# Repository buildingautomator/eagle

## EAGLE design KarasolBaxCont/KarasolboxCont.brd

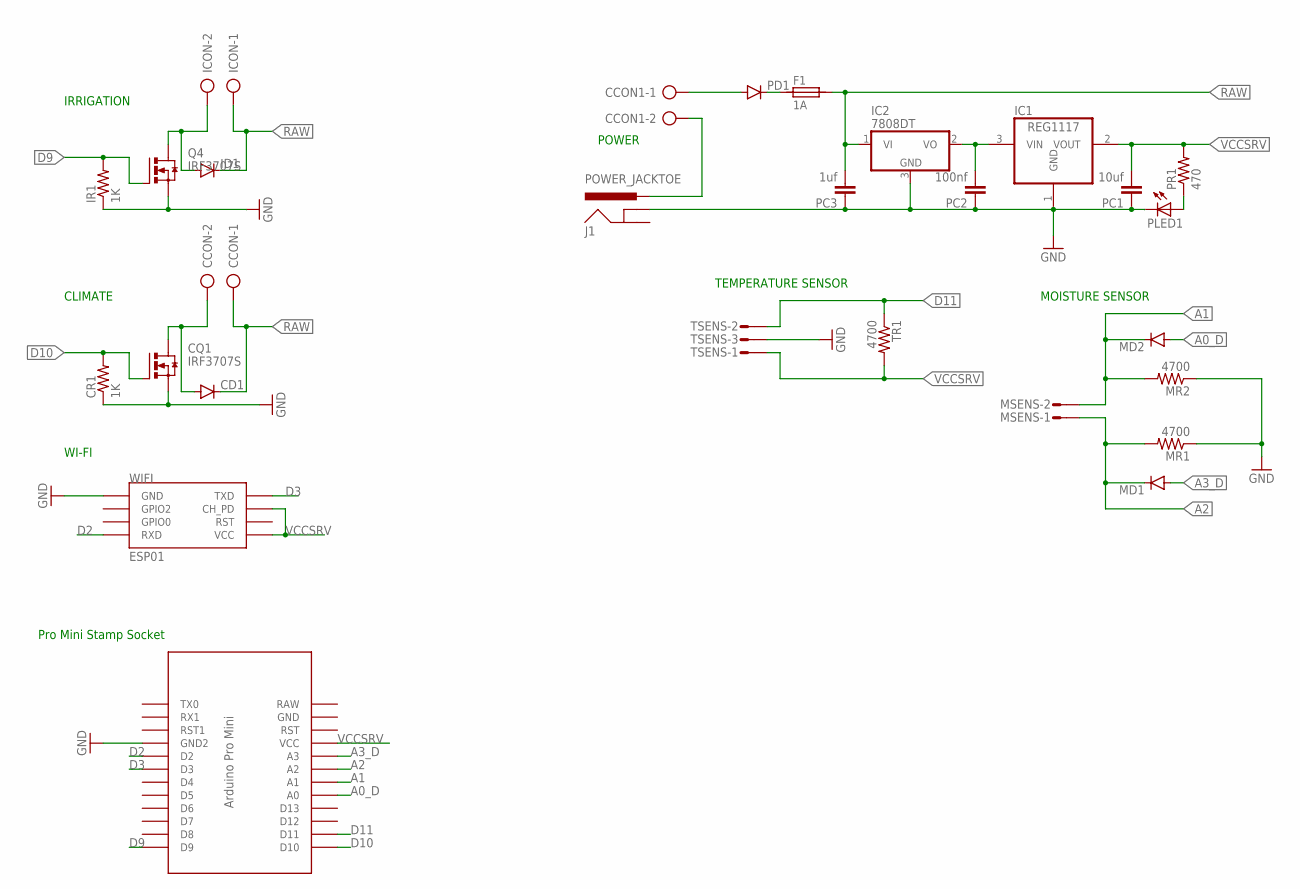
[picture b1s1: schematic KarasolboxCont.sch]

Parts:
CCON, CCON1: AK300/2
CD1: DIODESMA; SMA-DIODE
CQ1: IRF3707S; D2PACK
CR1: 1K; 0805
F1: 1A; 1820
IC1: REG1117; SOT223
IC2: 7808DT; TO252
ICON: AK300/2
ID1: DIODESMA; SMA-DIODE
IR1: 1K; 0805
J1: POWER_JACKTOE; POWER_JACK_SMD_OVERPASTE_TOE
MD1, MD2: DIODESMA; SMA-DIODE
MR1, MR2: 4700; 0805
MSENS: S02P
PC1: 10uf; 0805
PC2: 100nf; 0805
PC3: 1uf; 0805
PD1: DIODESMA; SMA-DIODE
PLED1: LEDCHIP-LED0805; CHIP-LED0805
PR1: 470; 0805
Q4: IRF3707S; D2PACK
TR1: 4700; 0805
TSENS: S03P
U$1: ABK-PRO-MINI
WIFI: ESP01

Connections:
A0_D: MD2.A, U$1.A0
A1: MD2.C, MR2.2, MSENS.2, U$1.A1
A2: MD1.C, MR1.2, MSENS.1, U$1.A2
A3_D: MD1.A, U$1.A3
D2: U$1.D2, WIFI.RX (RXD)
D3: U$1.D3, WIFI.TX (TXD)
D9: IR1.2, Q4.1 (G), U$1.D9
D10: CQ1.1 (G), CR1.2, U$1.D10
D11: TR1.1, TSENS.2, U$1.D11
GND: CQ1.3 (S), CR1.1, IC1.1 (GND), IC2.3 (GND), IR1.1, J1.GND (GNDBREAK), MR1.1, MR2.1, PC1.1, PC2.1, PC3.1, PLED1.C, Q4.3 (S), TSENS.3, U$1.GND1 (GND2), WIFI.GND
unnamed: F1.1, PD1.C
unnamed: CCON.2, CD1.A, CQ1.2 (D)
unnamed: CCON1.1, PD1.A
unnamed: ICON.2, ID1.A, Q4.2 (D)
unnamed: CCON1.2, J1.VIN0 (PWR)
unnamed: PLED1.A, PR1.1
unnamed: IC1.3 (VIN), IC2.2 (VO), PC2.2
RAW: CCON.1, CD1.C, F1.2, IC2.1 (VI), ICON.1, ID1.C, PC3.2
VCCSRV: IC1.2 (VOUT), PC1.2, PR1.2, TR1.2, TSENS.1, U$1.VCC, WIFI.CH_PD, WIFI.VCC

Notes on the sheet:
IRRIGATION
Pro Mini Stamp Socket
POWER
MOISTURE SENSOR
CLIMATE
TEMPERATURE SENSOR
WI-FI

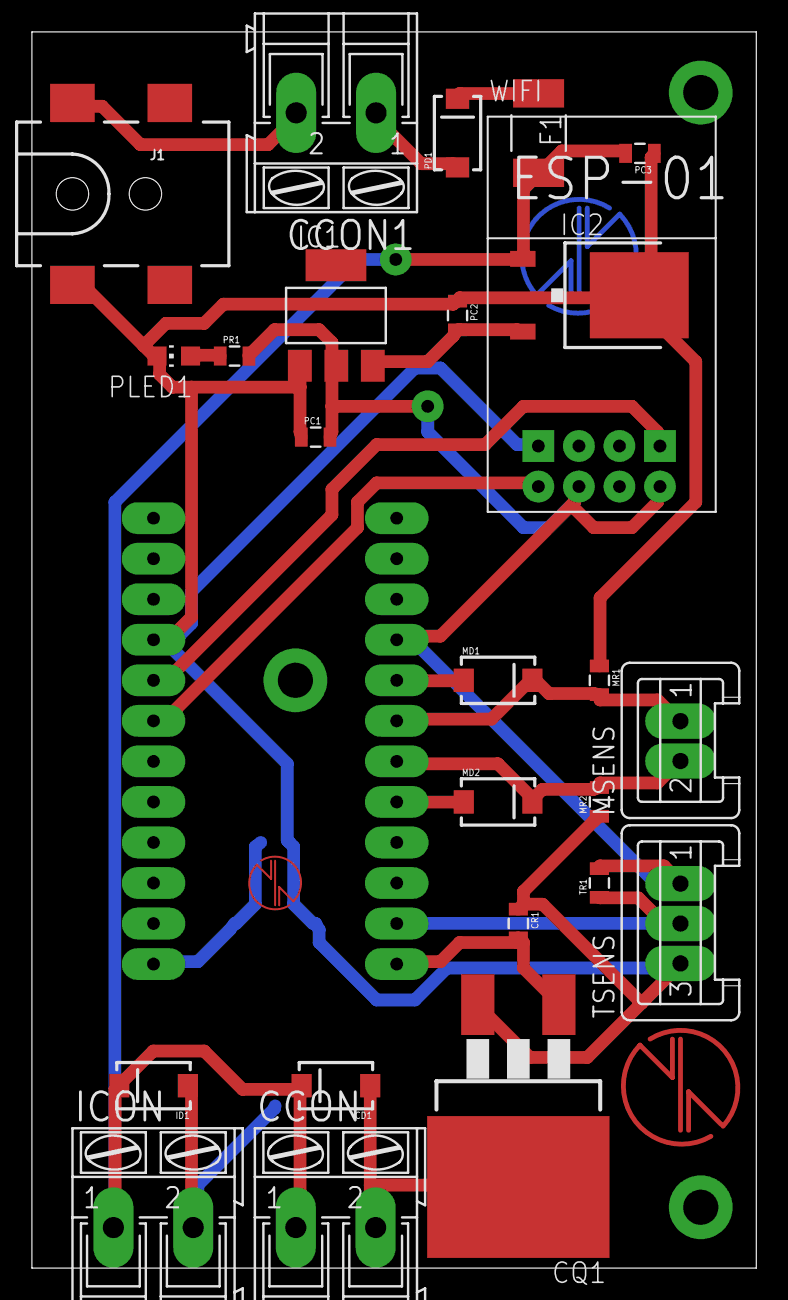
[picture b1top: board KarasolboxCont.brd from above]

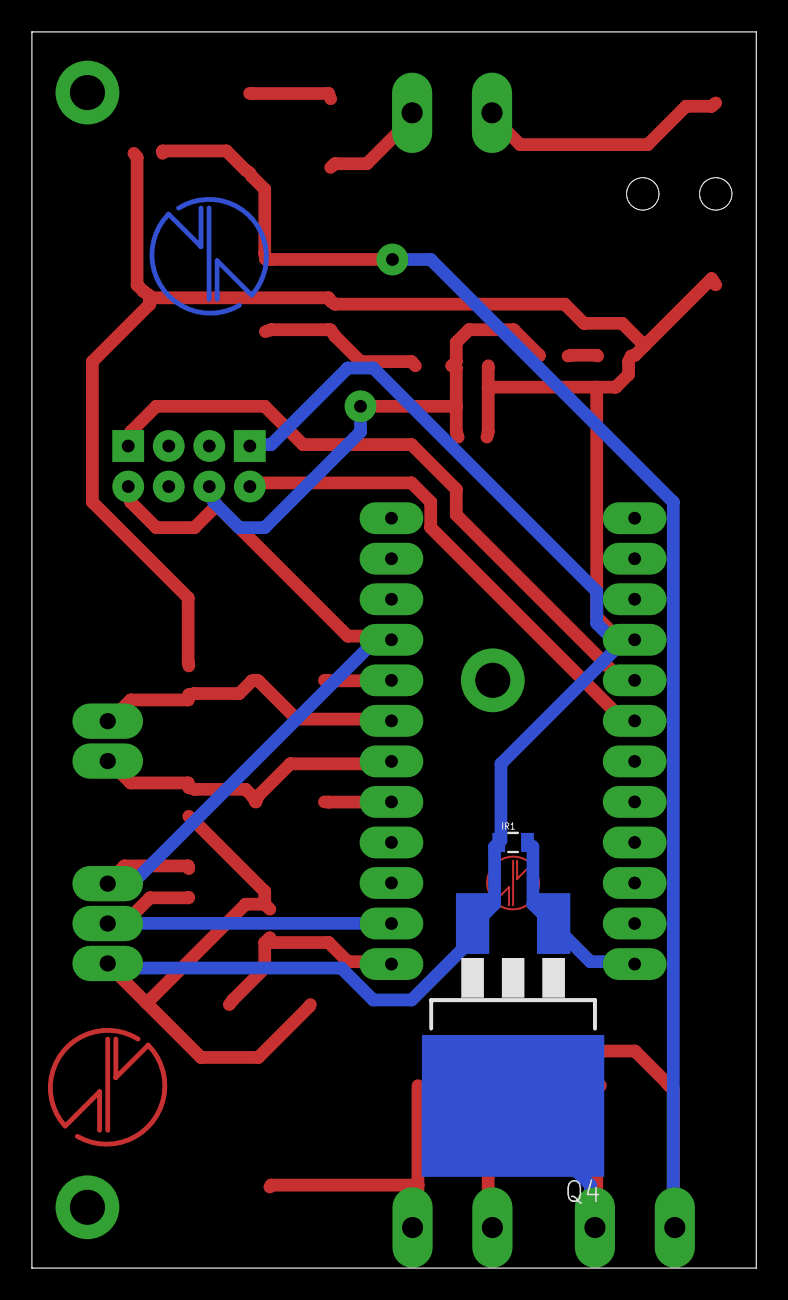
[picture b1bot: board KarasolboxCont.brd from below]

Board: 2 copper layers, 45.4 x 77.5 mm, 31 parts (3 on the bottom side), 19 nets.

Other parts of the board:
U$2: IOTECH_COPPER
U$3, U$4: IOTECH_COPPER_M

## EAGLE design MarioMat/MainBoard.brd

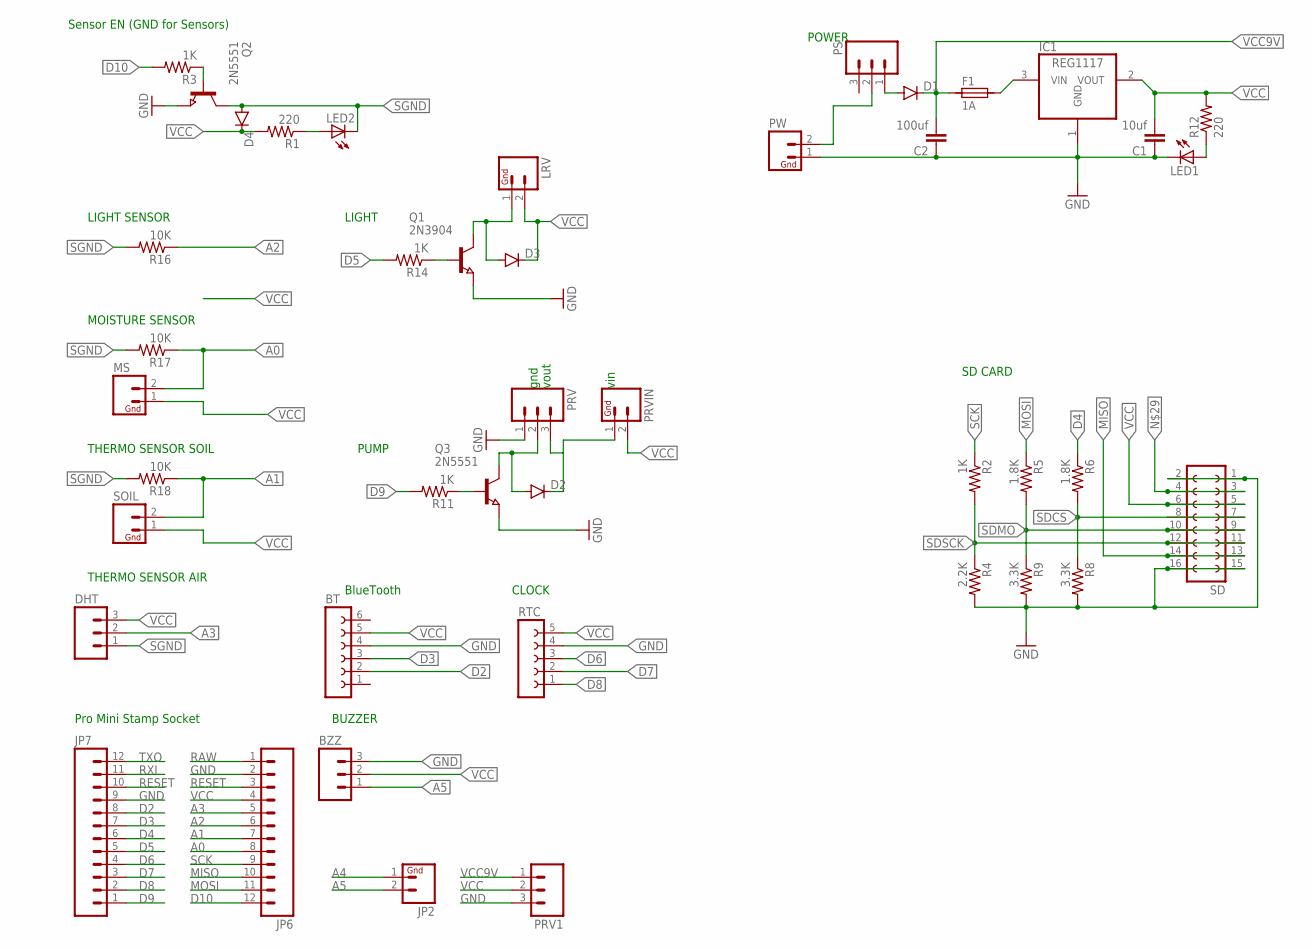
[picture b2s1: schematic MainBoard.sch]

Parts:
BT: FE06-1; FE06
BZZ: M03PTH; 1X03
C1: 10uf; 0805
C2: 100uf; 0805
D1, D2, D3, D4: DIODESMA; SMA-DIODE
DHT: M03PTH; 1X03
F1: 1A; 1820
IC1: REG1117; SOT223
JP2: M02PTH; 1X02
JP6, JP7: M12PTH; 1X12
LED1, LED2: LEDCHIP-LED0805; CHIP-LED0805
LRV: M02PTH; 1X02
MS: M02PTH; 1X02
PRV, PRV1: M03PTH; 1X03
PRVIN: M02PTH; 1X02
PS: M03PTH; 1X03
PW: M02PTH; 1X02
Q1: 2N3904; SOT23
Q2, Q3: 2N5551; SOT23
R1, R12: 220; 0805
R2, R3, R11, R14: 1K; 0805
R4: 2.2K; 0805
R5, R6: 1.8K; 0805
R8, R9: 3.3K; 0805
R16, R17, R18: 10K; 0805
RTC: FE05-1
SD: FE08-2
SOIL: M02PTH; 1X02

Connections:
A0: JP6.8, MS.2, R17.1
A1: JP6.7, R18.1, SOIL.2
A2: JP6.6, R16.1
A3: DHT.2, JP6.5
A4: JP2.1
A5: BZZ.1, JP2.2
D2: BT.2, JP7.8
D3: BT.3, JP7.7
D4: JP7.6, R6.1
D5: JP7.5, R14.2
D6: JP7.4, RTC.3
D7: JP7.3, RTC.2
D8: JP7.2, RTC.1
D9: JP7.1, R11.2
D10: JP6.12, R3.2
GND: BT.4, BZZ.3, C1.1, C2.1, IC1.1 (GND), JP6.2, JP7.9, LED1.C, PRV.1, PRV1.3, PW.1, Q1.2 (E), Q2.2 (E), Q3.2 (E), R4.2, R8.2, R9.2, RTC.4, SD.1, SD.2, SD.15, SD.16
MISO: JP6.10, SD.13, SD.14
MOSI: JP6.11, R5.1
unnamed: F1.2, IC1.3 (VIN)
unnamed: PS.2, PW.2
unnamed: D2.C, PRV.3, PRVIN.1
unnamed: D2.A, PRV.2, Q3.3 (C)
unnamed: Q3.1 (B), R11.1
unnamed: Q2.1 (B), R3.1
unnamed: LED1.A, R12.1
unnamed: D1.A, PS.1
unnamed: D3.A, LRV.1, Q1.3 (C)
unnamed: Q1.1 (B), R14.1
unnamed: LED2.A, R1.1
unnamed: SD.3, SD.4
RAW: JP6.1
RESET: JP6.3, JP7.10
RXI: JP7.11
SCK: JP6.9, R2.1
SDCS: R6.2, R8.1, SD.7, SD.8
SDMO: R5.2, R9.1, SD.9, SD.10
SDSCK: R2.2, R4.1, SD.11, SD.12
SGND: D4.A, DHT.1, LED2.C, Q2.3 (C), R16.2, R17.2, R18.2
TXO: JP7.12
VCC: BT.5, BZZ.2, C1.2, D3.C, D4.C, DHT.3, IC1.2 (VOUT), JP6.4, LRV.2, MS.1, PRV1.2, PRVIN.2, R1.2, R12.2, RTC.5, SD.5, SD.6, SOIL.1
VCC9V: C2.2, D1.C, F1.1, PRV1.1

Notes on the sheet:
PUMP
Pro Mini Stamp Socket
Sensor EN (GND for Sensors)
POWER
LIGHT
LIGHT SENSOR
MOISTURE SENSOR
THERMO SENSOR SOIL
THERMO SENSOR AIR
CLOCK
BlueTooth
SD CARD
vin
vout
gnd
BUZZER

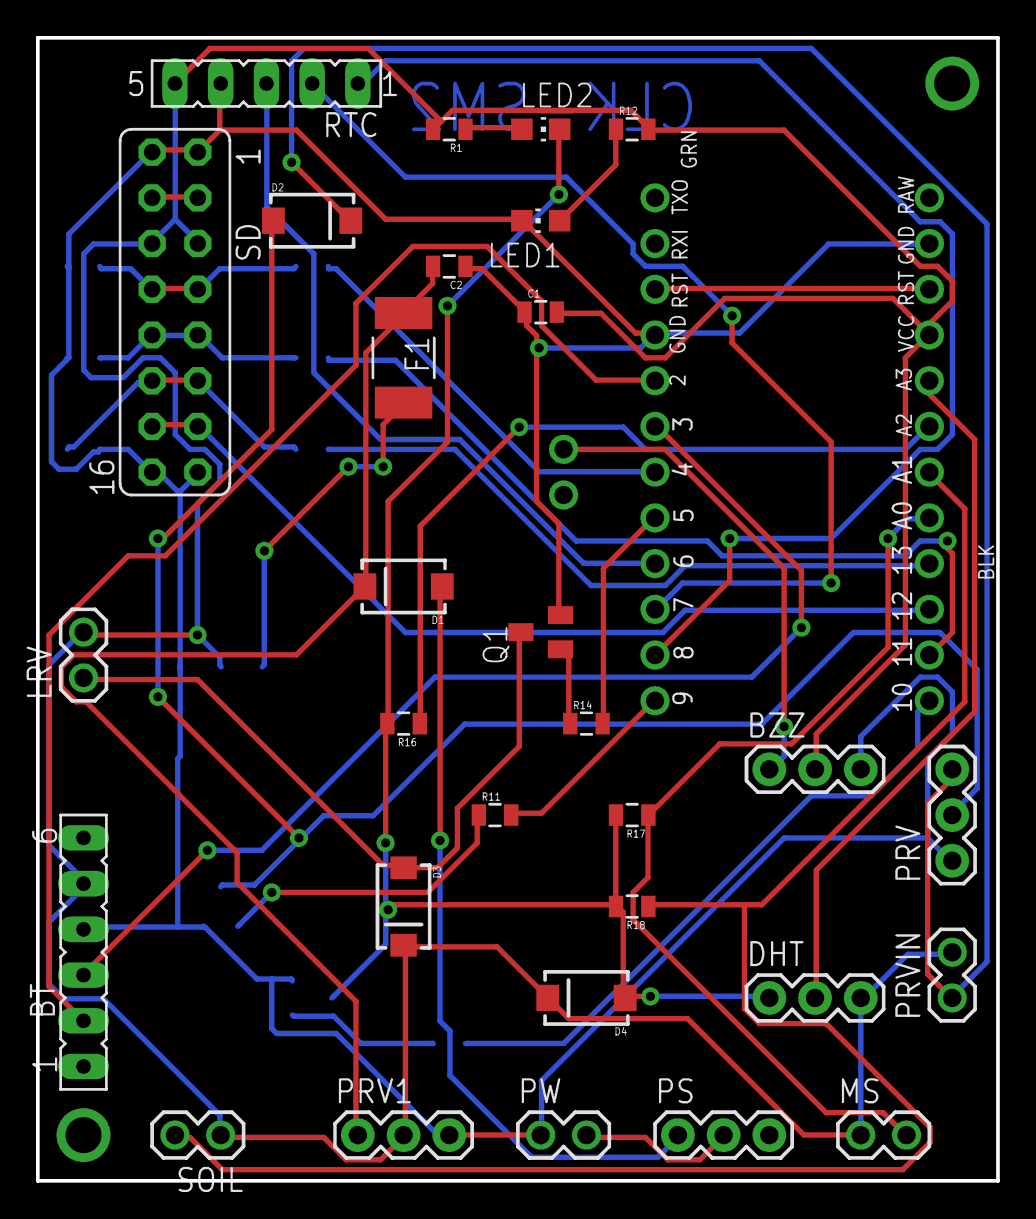
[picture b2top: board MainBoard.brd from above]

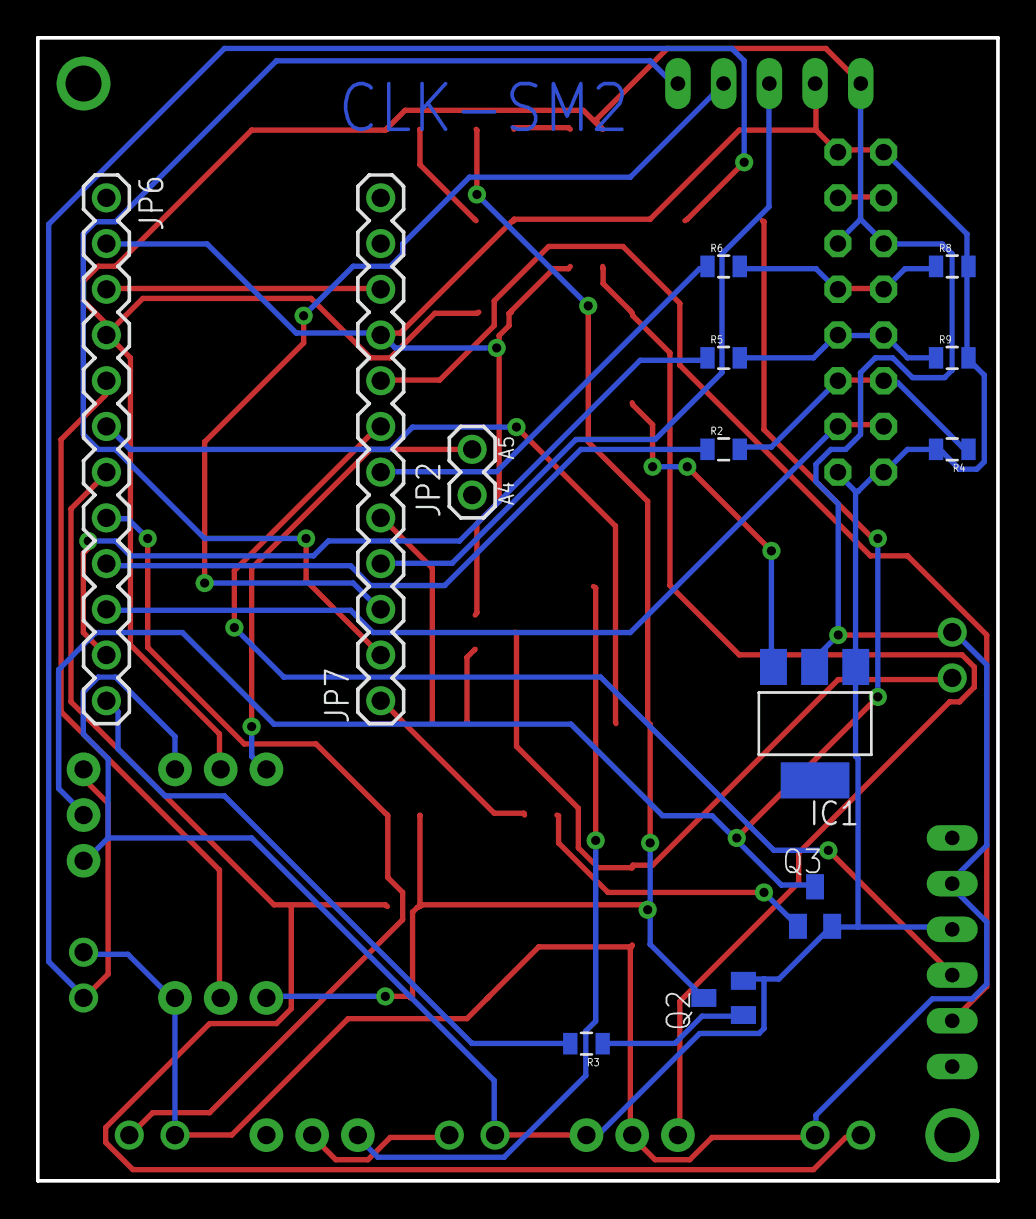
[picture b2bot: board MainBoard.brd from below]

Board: 2 copper layers, 53.3 x 63.5 mm, 43 parts (13 on the bottom side), 37 nets.

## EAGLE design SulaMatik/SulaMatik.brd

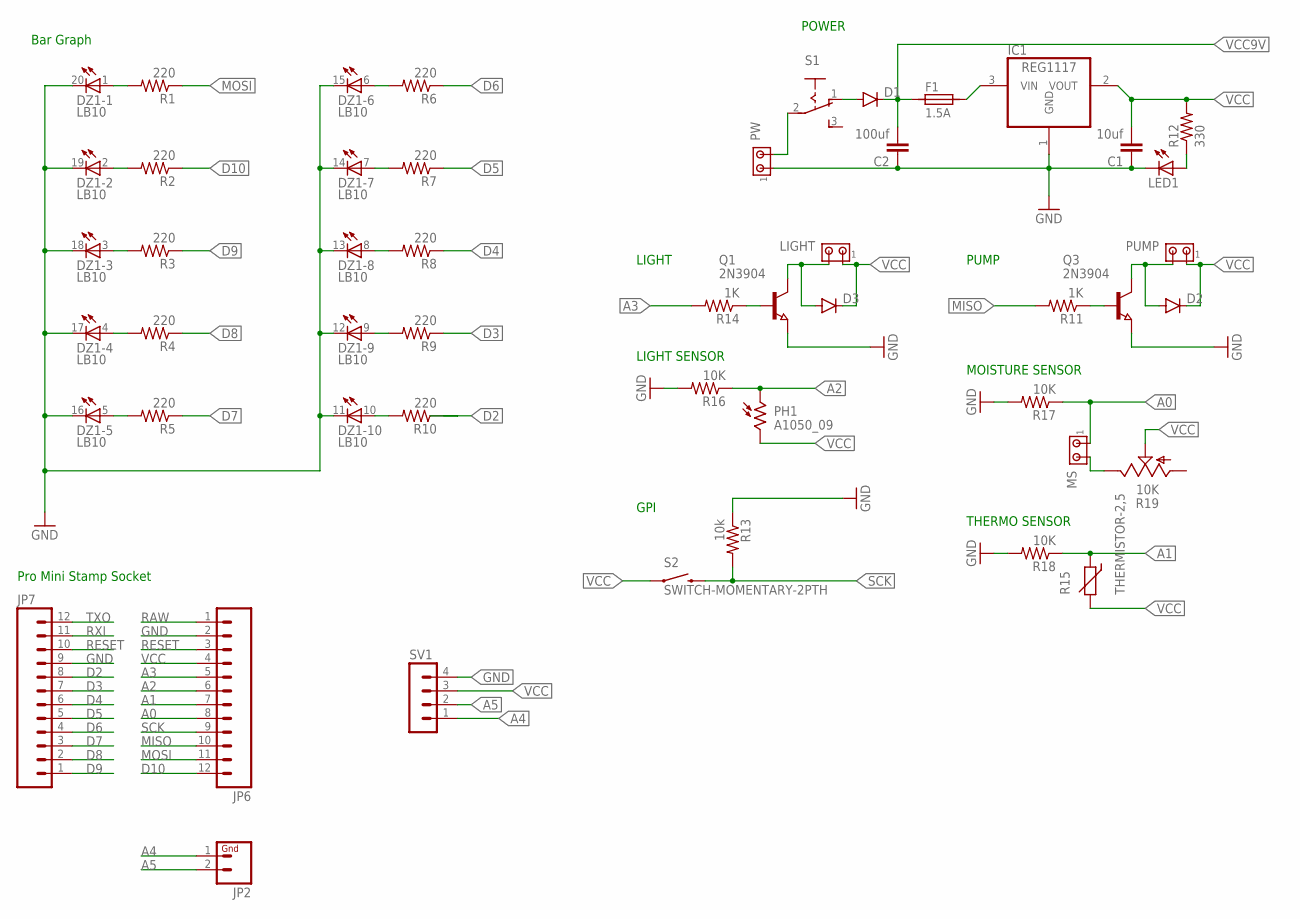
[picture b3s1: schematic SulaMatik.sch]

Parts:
C1: 10uf; 0805
C2: 100uf; 0805
D1, D2, D3: DIODESMA; SMA-DIODE
DZ1: LB10
F1: 1.5A; 1820
IC1: REG1117; SOT223
JP2: M02PTH; 1X02
JP6, JP7: M12PTH; 1X12
LED1: LEDCHIP-LED0805; CHIP-LED0805
LIGHT: MTA02-156; 1X2MTA
MS: MTA02-156; 1X2MTA
PH1: A1050_09; T0-46-A10XX
PUMP: MTA02-156; 1X2MTA
PW: MTA02-156; 1X2MTA
Q1, Q3: 2N3904; SOT23
R1, R2, R3, R4, R5, R6, R7, R8, R9, R10: 220; 0805
R11, R14: 1K; 0805
R12: 330; 0805
R13: 10k; 0805
R15: THERMISTOR-2,5; RS-2,5
R16, R17, R18: 10K; 0805
R19: 10K; CA6V
S1: 255SB
S2: SWITCH-MOMENTARY-2PTH; TACTILE-PTH
SV1: MA04-1

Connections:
A0: JP6.8, MS.1, R17.1
A1: JP6.7, R15.1, R18.1
A2: JP6.6, PH1.1, R16.1
A3: JP6.5, R14.2
A4: JP2.1, SV1.1
A5: JP2.2, SV1.2
D2: JP7.8, R10.1
D3: JP7.7, R9.1
D4: JP7.6, R8.1
D5: JP7.5, R7.1
D6: JP7.4, R6.1
D7: JP7.3, R5.1
D8: JP7.2, R4.1
D9: JP7.1, R3.1
D10: JP6.12, R2.1
GND: C1.1, C2.1, DZ1.11 (C), DZ1.12 (C), DZ1.13 (C), DZ1.14 (C), DZ1.15 (C), DZ1.16 (C), DZ1.17 (C), DZ1.18 (C), DZ1.19 (C), DZ1.20 (C), IC1.1 (GND), JP6.2, JP7.9, LED1.C, PW.1, Q1.2 (E), Q3.2 (E), R13.1, R16.2, R17.2, R18.2, SV1.4
MISO: JP6.10, R11.2
MOSI: JP6.11, R1.1
unnamed: F1.2, IC1.3 (VIN)
unnamed: PW.2, S1.2
unnamed: DZ1.5 (A), R5.2
unnamed: DZ1.4 (A), R4.2
unnamed: D2.A, PUMP.2, Q3.3 (C)
unnamed: Q3.1 (B), R11.1
unnamed: DZ1.3 (A), R3.2
unnamed: DZ1.2 (A), R2.2
unnamed: DZ1.1 (A), R1.2
unnamed: DZ1.6 (A), R6.2
unnamed: LED1.A, R12.1
unnamed: DZ1.7 (A), R7.2
unnamed: D1.A, S1.1 (O)
unnamed: DZ1.8 (A), R8.2
unnamed: DZ1.9 (A), R9.2
unnamed: DZ1.10 (A), R10.2
unnamed: MS.2, R19.E
unnamed: D3.A, LIGHT.2, Q1.3 (C)
unnamed: Q1.1 (B), R14.1
RAW: JP6.1
RESET: JP6.3, JP7.10
RXI: JP7.11
SCK: JP6.9, R13.2, S2.3 (2)
TXO: JP7.12
VCC: C1.2, D2.C, D3.C, IC1.2 (VOUT), JP6.4, LIGHT.1, PH1.2, PUMP.1, R12.2, R15.2, R19.S, S2.1, SV1.3
VCC9V: C2.2, D1.C, F1.1

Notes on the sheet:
PUMP
Pro Mini Stamp Socket
Bar Graph
POWER
GPI
LIGHT
LIGHT SENSOR
MOISTURE SENSOR
THERMO SENSOR

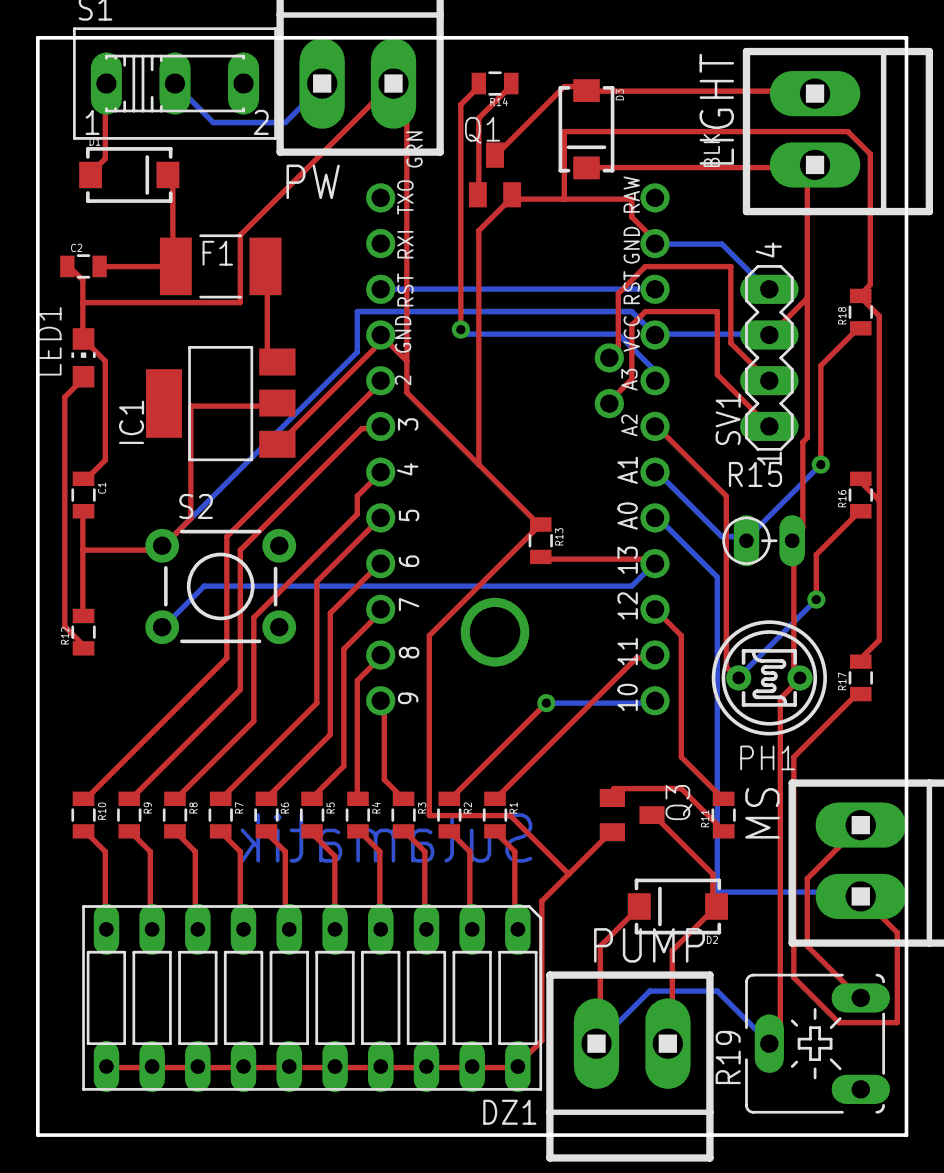
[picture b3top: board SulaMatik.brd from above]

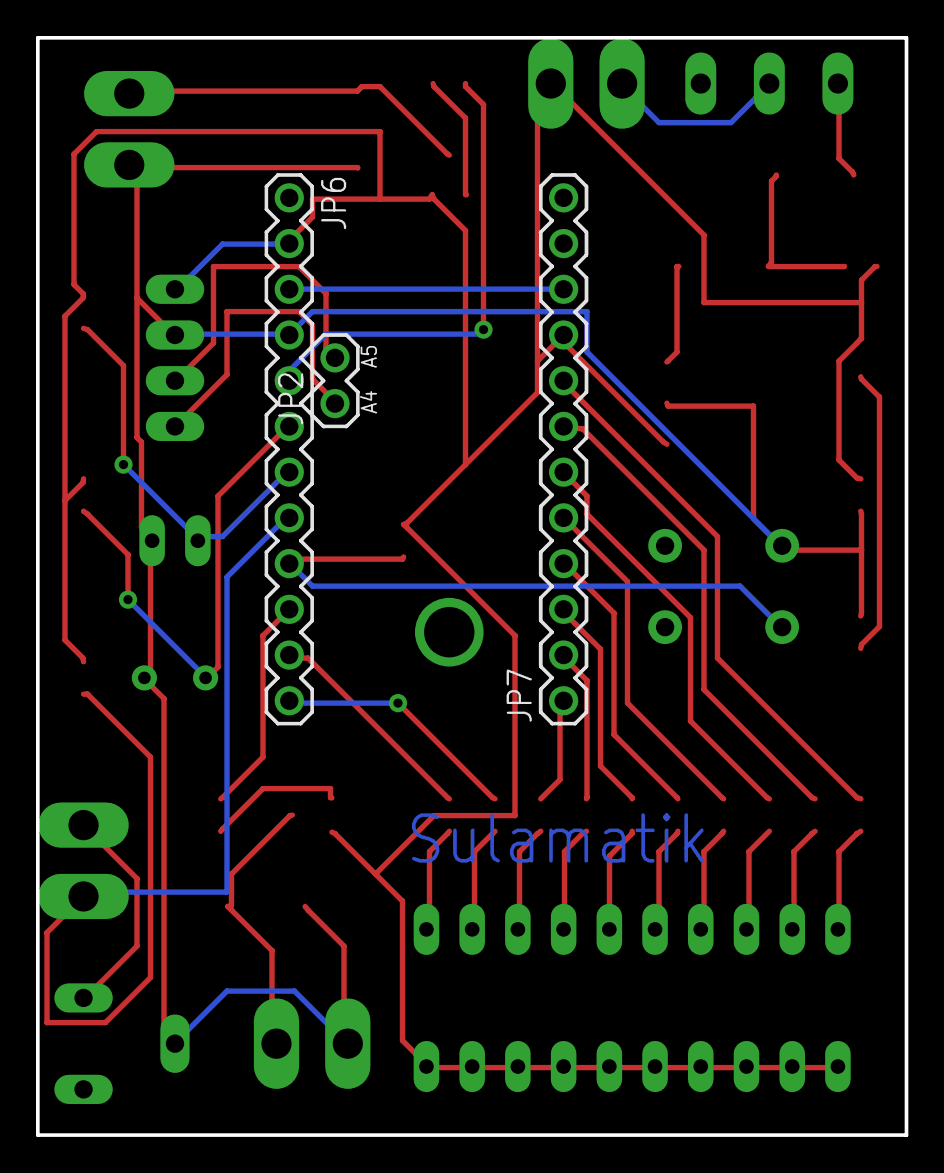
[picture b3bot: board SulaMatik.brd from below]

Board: 2 copper layers, 48.3 x 61.0 mm, 41 parts (3 on the bottom side), 41 nets.

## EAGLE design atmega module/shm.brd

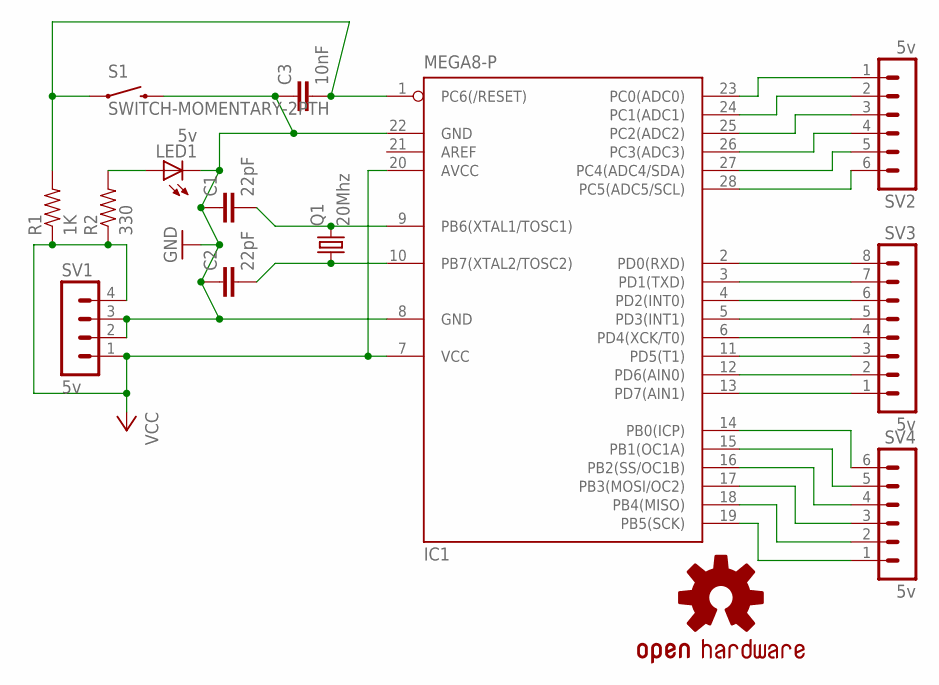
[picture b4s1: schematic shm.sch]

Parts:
C1, C2: 22pF; 0805
C3: 10nF; 0805
IC1: MEGA8-P; DIL28-3
LED1: 5v; CHIPLED_0805
LOGO1: OSHW-LOGOL; OSHW-LOGO-L
Q1: 20Mhz; SM49
R1: 1K; 0805
R2: 330; 0805
S1: SWITCH-MOMENTARY-2PTH; TACTILE-PTH
SV1: 5v; MA04-1
SV2, SV4: 5v; MA06-1
SV3: 5v; MA08-1

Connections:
GND: C1.1, C2.1, C3.1, IC1.8 (GND), IC1.22 (GND), LED1.C, S1.3 (2), SV1.2, SV1.3
unnamed: IC1.2 (PD0(RXD)), SV3.8
unnamed: IC1.3 (PD1(TXD)), SV3.7
unnamed: IC1.4 (PD2(INT0)), SV3.6
unnamed: IC1.5 (PD3(INT1)), SV3.5
unnamed: IC1.6 (PD4(XCK/T0)), SV3.4
unnamed: IC1.11 (PD5(T1)), SV3.3
unnamed: IC1.12 (PD6(AIN0)), SV3.2
unnamed: IC1.13 (PD7(AIN1)), SV3.1
unnamed: IC1.14 (PB0(ICP)), SV4.6
unnamed: IC1.15 (PB1(OC1A)), SV4.5
unnamed: IC1.16 (PB2(SS/OC1B)), SV4.4
unnamed: IC1.17 (PB3(MOSI/OC2)), SV4.3
unnamed: IC1.18 (PB4(MISO)), SV4.2
unnamed: IC1.19 (PB5(SCK)), SV4.1
unnamed: IC1.28 (PC5(ADC5/SCL)), SV2.6
unnamed: IC1.27 (PC4(ADC4/SDA)), SV2.5
unnamed: IC1.26 (PC3(ADC3)), SV2.4
unnamed: IC1.25 (PC2(ADC2)), SV2.3
unnamed: IC1.24 (PC1(ADC1)), SV2.2
unnamed: IC1.23 (PC0(ADC0)), SV2.1
unnamed: C1.2, IC1.9 (PB6(XTAL1/TOSC1)), Q1.2
unnamed: LED1.A, R2.2
unnamed: C2.2, IC1.10 (PB7(XTAL2/TOSC2)), Q1.1
unnamed: C3.2, IC1.1 (PC6(/RESET)), R1.2, S1.1
VCC: IC1.7 (VCC), IC1.20 (AVCC), R1.1, R2.1, SV1.1, SV1.4

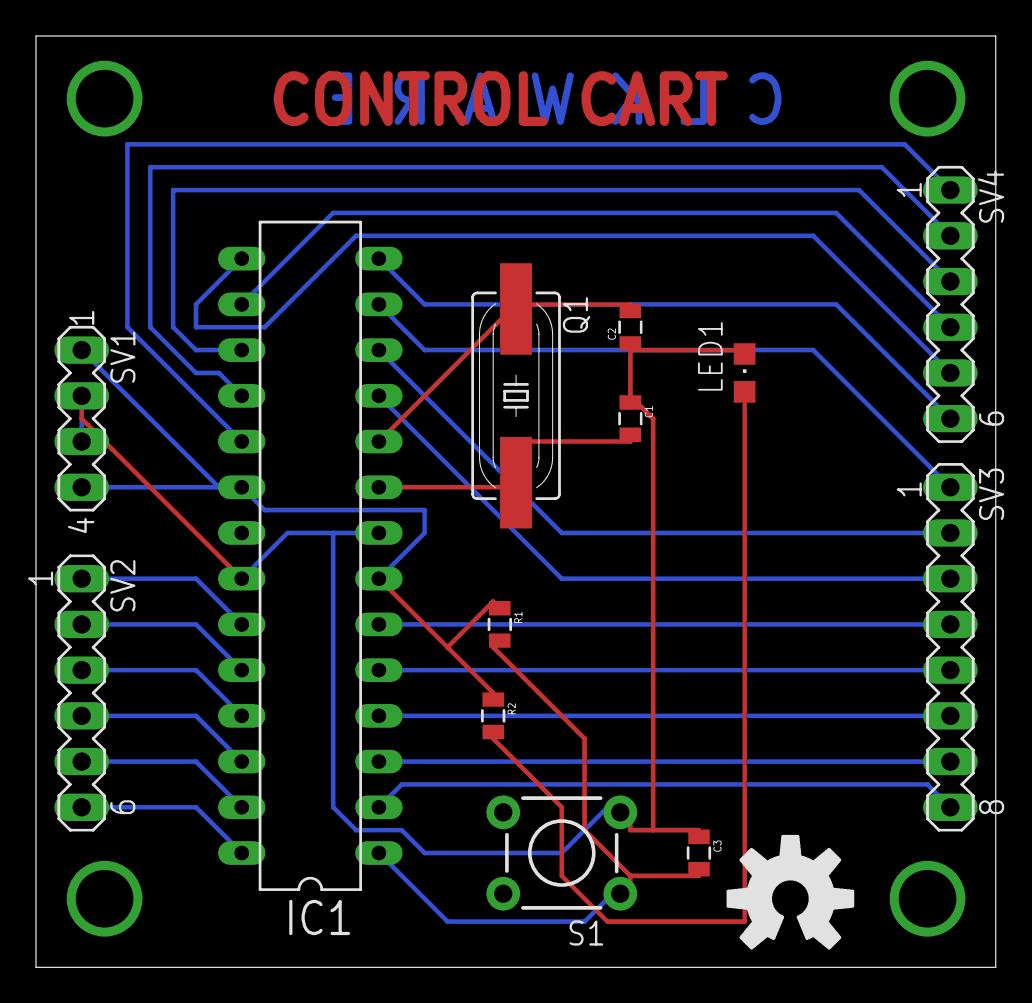
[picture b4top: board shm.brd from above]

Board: 2 copper layers, 53.3 x 51.7 mm, 14 parts (0 on the bottom side), 26 nets.

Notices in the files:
parts and their libraries:
SparkFun-Capacitors: Licensing: Creative Commons ShareAlike 4.0 International - https://creativecommons.org/licenses/by-sa/4.0
